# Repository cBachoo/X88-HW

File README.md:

# X88H - Hybrid USB/JST

## License

This work is licensed under a [Creative Commons Attribution-ShareAlike 4.0 International License](https://creativecommons.org/licenses/by-sa/4.0/).

You are free to produce, modify, manufacture, and distribute this design, including for commercial purposes, provided you give appropriate credit and license any derivative works under the same terms.

Questions? Contact Bachoo (`bachoobusiness[at]gmail.com`).

[![CC BY-SA 4.0][cc-by-sa-image]][cc-by-sa]

[cc-by-sa]: http://creativecommons.org/licenses/by-sa/4.0/
[cc-by-sa-image]: https://licensebuttons.net/l/by-sa/4.0/88x31.png
[cc-by-sa-shield]: https://img.shields.io/badge/License-CC%20BY--SA%204.0-lightgrey.svg

## Changelog

- 17 Aug 2024
    - Rotated JST connector so it's facing the alphas

## Design Files / Libraries

The files were designed with [KiCAD 8.0.4](https://www.kicad.org/).

The [marbastlib](https://github.com/ebastler/marbastlib) MX switch symbol/footprint library is used for the project.

The 3D model for the PCB can be seen in the main folder under `X88H-3D-model.step`.

## Ordering from JLCPCB

1) Head to the [JLCPCB order page](https://cart.jlcpcb.com/quote).

2) Upload the `GERBER-X88H.zip` file in `jlcpcb/production_files/`.

3) Set the quantity of the PCBs you want made.

4) Set your desired PCB parameters. Here are some suggested parameters: (Everything else can be kept at their default)

- PCB Color: **Black**
- Surface Finish: **ENIG**
- Remove Order Number: **Yes**   

5) Enable the PCB Assembly option at the bottom, and set the following parameters:

- PCBA Type: **Standard**
- Assembly Side: **Both Sides**

6) Press `Confirm` at the bottom or `NEXT` on the right to get to the next page.

7) Click `NEXT` to get to the Bill of Materials tab.

8) Click `Add BOM File` and select the `BOM-X88H.csv` file in `jlcpcb/production_files/`.

9) Click `Add CPL File` and select the `CPL-X88H.csv` file in `jlcpcb/production_files/`. Click `Process BOM & CPL` to proceed.

10) You should be presented with a list of all the components and quantities needed. Double check there are no missing components. If there are, you will have to find substitute components for it. Click `NEXT` to proceed.

11) You should be presented with a view of the PCB and its components. Click `NEXT` to proceed.

12) You should see a breakdown of the price for the PCBs you want to order. Select `Keyboard - HS Code 847330` under `Office Appliance Accessories` for the Product Description.

13) Save to cart, and pay for it!

## Ordering from PCBWay

1) Head to the [PCBWay Quick Order page](https://www.pcbway.com/QuickOrderOnline.aspx)

2) Click the `Add Gerber file` button and add the `X88H.kicad_pcb.zip` file in the main folder. Don't worry about the broken preview.

3) Set the quantity of the PCBs you want made.

4) Set your desired PCB parameters. Here are some suggested parameters: (Everything else can be kept at their default)

- Solder mask: **Black**
- Surface finish: **Immersion gold (ENIG)**
- Remove product no.: **Yes (extra+$1.5)**

5) Enable the Assembly Service option at the bottom, and set the following parameters:

- Assembly side(s): **Both sides**
- Quantity: **as needed; same number as your PCBs?**
- Do you accept alternatives/substitutes made in China? **Yes**

6) Click Save to Cart. You will have to wait for your order to be reviewed before you can pay for it.

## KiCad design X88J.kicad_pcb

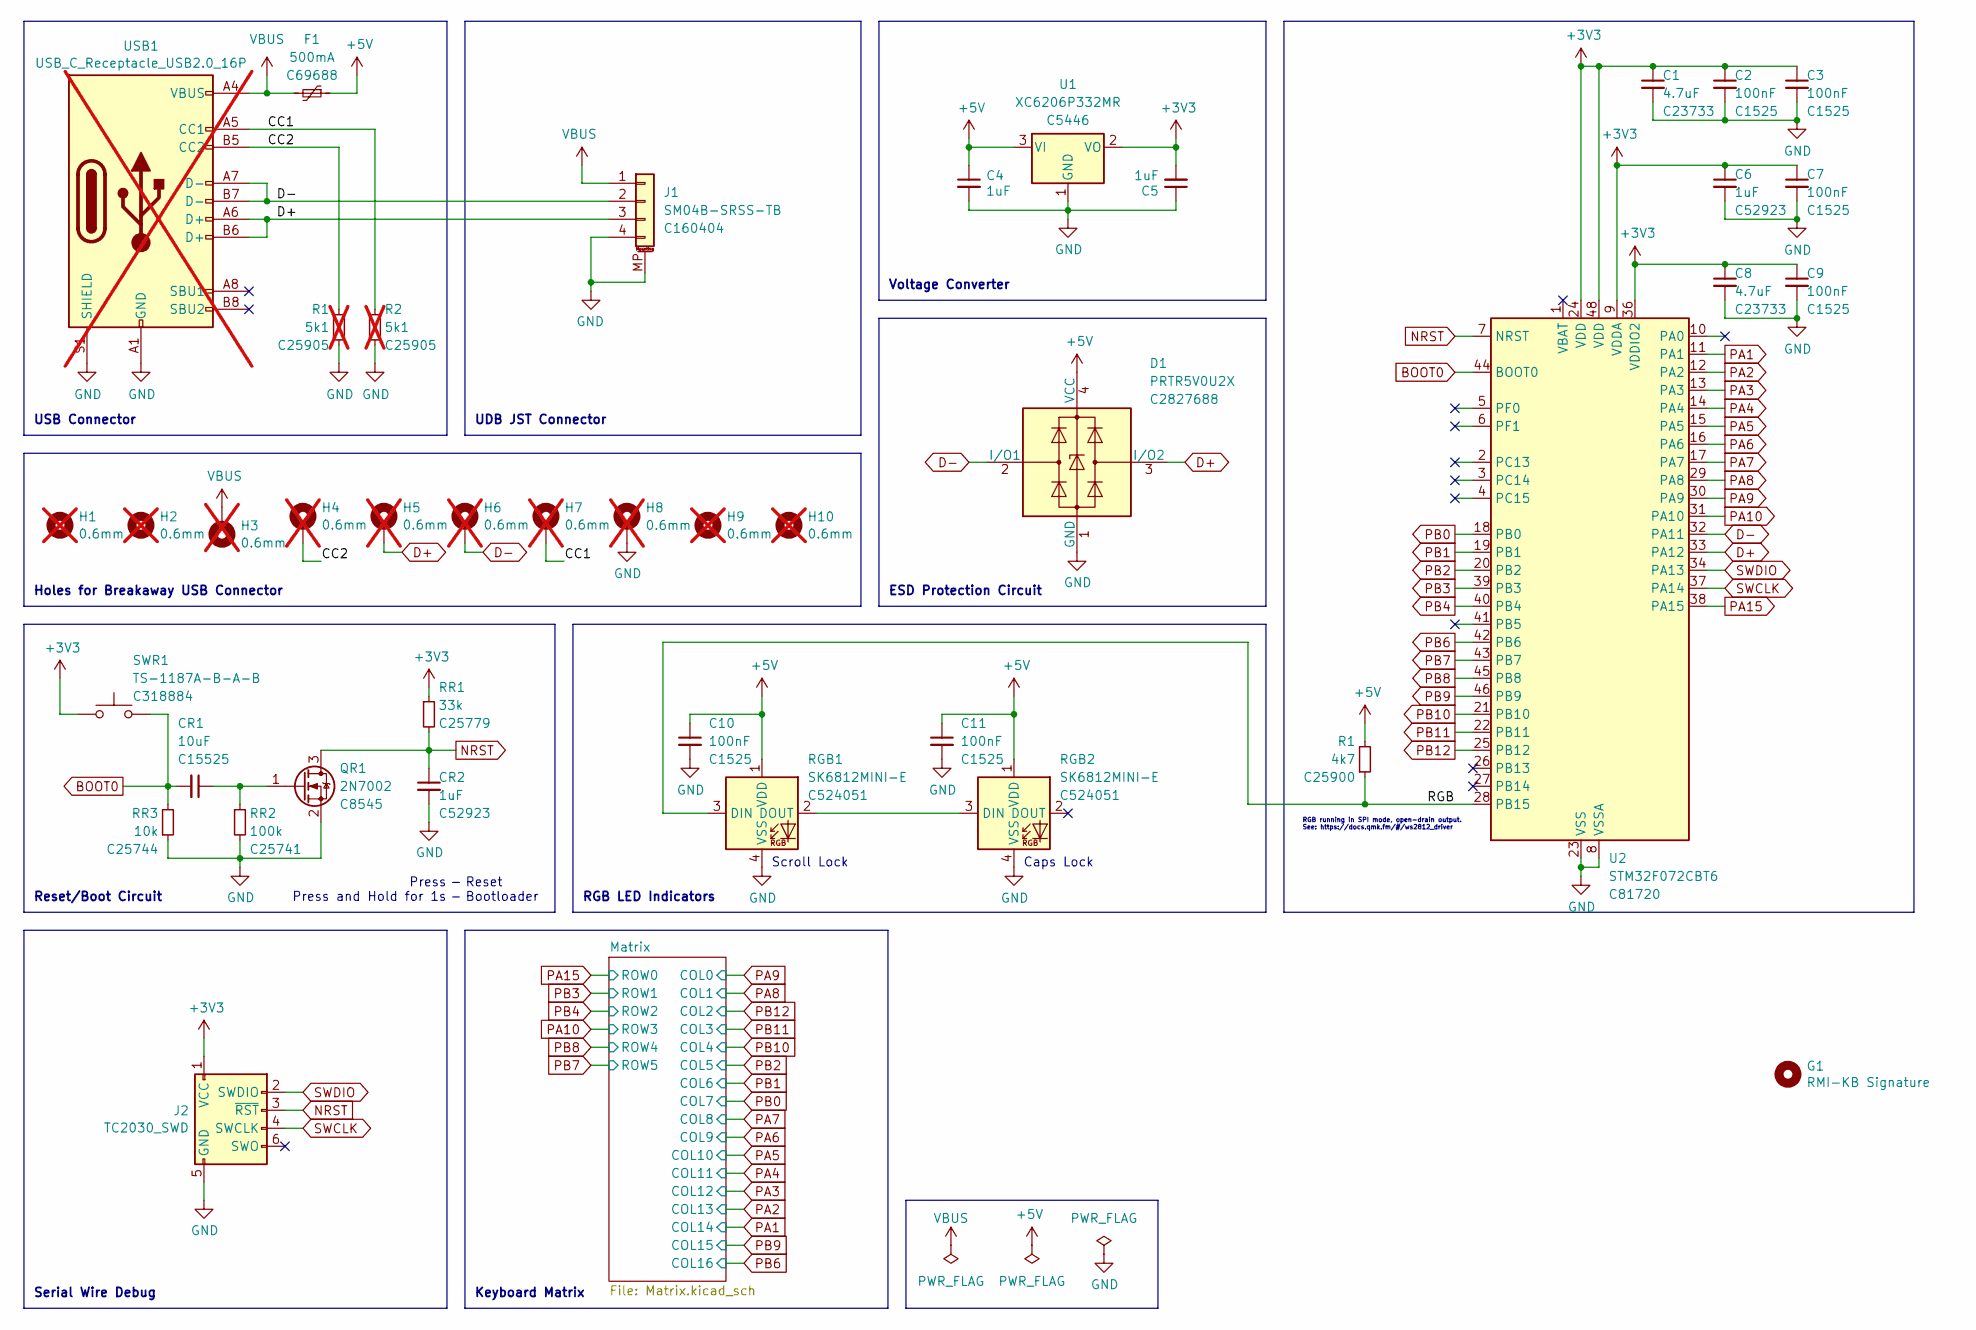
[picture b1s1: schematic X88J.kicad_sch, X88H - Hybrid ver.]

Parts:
C1, C8: 4.7uF; C_0402_1005Metric; MPN CL05A475MP5NRNC; LCSC C23733
C2, C3, C7, C9, C10, C11: 100nF; C_0402_1005Metric; MPN CL05B104KO5NNNC; LCSC C1525
C4, C5, C6: 1uF; C_0402_1005Metric; MPN CL05A105KA5NQNC; LCSC C52923
CR1: 10uF; C_0402_1005Metric; MPN CL05A106MQ5NUNC; LCSC C15525
CR2: 1uF; C_0402_1005Metric; MPN CL05A105KA5NQNC; LCSC C52923
D1: PRTR5V0U2X; SOT-143; MPN PRTR5V0U2X; LCSC C2827688
F1: 500mA; Fuse_1206_3216Metric_Pad1.42x1.75mm_HandSolder; MPN nSMD050; LCSC C69688
G1: RMI-KB Signature; Signature
H1, H2, H9, H10: 0.6mm; Hole_0.6mm; not fitted
H3, H4, H5, H6, H7, H8: 0.6mm; Hole_0.6mm_Pad; not fitted
J1: SM04B-SRSS-TB; JST_SH_SM04B-SRSS-TB_1x04-1MP_P1.00mm_Horizontal; MPN SM04B-SRSS-TB(LF)(SN); LCSC C160404
J2: TC2030_SWD; CON_TC2030_outlined
QR1: 2N7002; SOT-23; MPN 2N7002; LCSC C8545
R1, R2: 5k1; R_0402_1005Metric; MPN 0402WGF5101TCE; LCSC C25905; not fitted
RGB1, RGB2: SK6812MINI-E; LED_6028R; MPN SK6812MINI-E; LCSC C524051
RR1: 33k; R_0402_1005Metric; MPN 0402WGF3302TCE; LCSC C25779
RR2: 100k; R_0402_1005Metric; MPN 0402WGF1003TCE; LCSC C25741
RR3: 10k; R_0402_1005Metric; MPN 0402WGF1002TCE; LCSC C25744
SWR1: TS-1187A-B-A-B; SW_SPST_TL3342; MPN TS-1187A-B-A-B; LCSC C318884
U1: XC6206P332MR; SOT-23; MPN XC6206P332MR-G; LCSC C5446
U2: STM32F072CBT6; LQFP-48_7x7mm_P0.5mm; MPN STM32F072CBT6; LCSC C81720
USB1: USB_C_Receptacle_USB2.0_16P; USB_C_Receptacle_HRO_TYPE-C-31-M-12; MPN TYPE-C-31-M-12; LCSC C165948; not fitted

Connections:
+3V3: C1.1, C2.1, C3.1, C5.2, C6.1, C7.1, C8.1, C9.1, J2.1 (VCC), RR1.1, SWR1.1, U1.2 (VO), U2.9 (VDDA), U2.24 (VDD), U2.36 (VDDIO2), U2.48 (VDD)
+5V: C4.1, C10.1, C11.1, D1.4 (VCC), F1.1, RGB1.1 (VDD), RGB2.1 (VDD), U1.3 (VI); also elsewhere on the board
/RGB: RGB1.3 (DIN), U2.28 (PB15); also elsewhere on the board
D+: D1.3 (I/O2), H5.1, J1.3, U2.33 (PA12), USB1.A6 (D+), USB1.B6 (D+)
D-: D1.2 (I/O1), H6.1, J1.2, U2.32 (PA11), USB1.A7 (D-), USB1.B7 (D-)
NRST: CR2.1, J2.3 (~RST), QR1.3 (D), RR1.2, U2.7 (NRST)
unnamed: H4.1, R1.1, USB1.B5 (CC2)
unnamed: H7.1, R2.1, USB1.A5 (CC1)
unnamed: RGB1.2 (DOUT), RGB2.3 (DIN)
PA1: U2.11 (PA1); also elsewhere on the board
PA2: U2.12 (PA2); also elsewhere on the board
PA3: U2.13 (PA3); also elsewhere on the board
PA4: U2.14 (PA4); also elsewhere on the board
PA5: U2.15 (PA5); also elsewhere on the board
PA6: U2.16 (PA6); also elsewhere on the board
PA7: U2.17 (PA7); also elsewhere on the board
PA8: U2.29 (PA8); also elsewhere on the board
PA9: U2.30 (PA9); also elsewhere on the board
PA10: U2.31 (PA10); also elsewhere on the board
PA15: U2.38 (PA15); also elsewhere on the board
PB0: U2.18 (PB0); also elsewhere on the board
PB1: U2.19 (PB1); also elsewhere on the board
PB2: U2.20 (PB2); also elsewhere on the board
PB3: U2.39 (PB3); also elsewhere on the board
PB4: U2.40 (PB4); also elsewhere on the board
PB6: U2.42 (PB6); also elsewhere on the board
PB7: U2.43 (PB7); also elsewhere on the board
PB8: U2.45 (PB8); also elsewhere on the board
PB9: U2.46 (PB9); also elsewhere on the board
PB10: U2.21 (PB10); also elsewhere on the board
PB11: U2.22 (PB11); also elsewhere on the board
PB12: U2.25 (PB12); also elsewhere on the board
SWCLK: J2.4 (SWCLK), U2.37 (PA14)
SWDIO: J2.2 (SWDIO), U2.34 (PA13)
VBUS: F1.2, H3.1, J1.1, USB1.A4 (VBUS), USB1.A9 (VBUS), USB1.B4 (VBUS), USB1.B9 (VBUS)

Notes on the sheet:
Holes for Breakaway USB Connector
Reset Bootloader
ESD Protection Circuit
Caps Lock
RGB running in SPI mode, open-drain output. See: https://docs.qmk.fm/#/ws2812_driver
- -
UDB JST Connector
RGB LED Indicators
Voltage Converter
Press Press and Hold for 1s
Reset/Boot Circuit
Serial Wire Debug
Keyboard Matrix
USB Connector
Scroll Lock

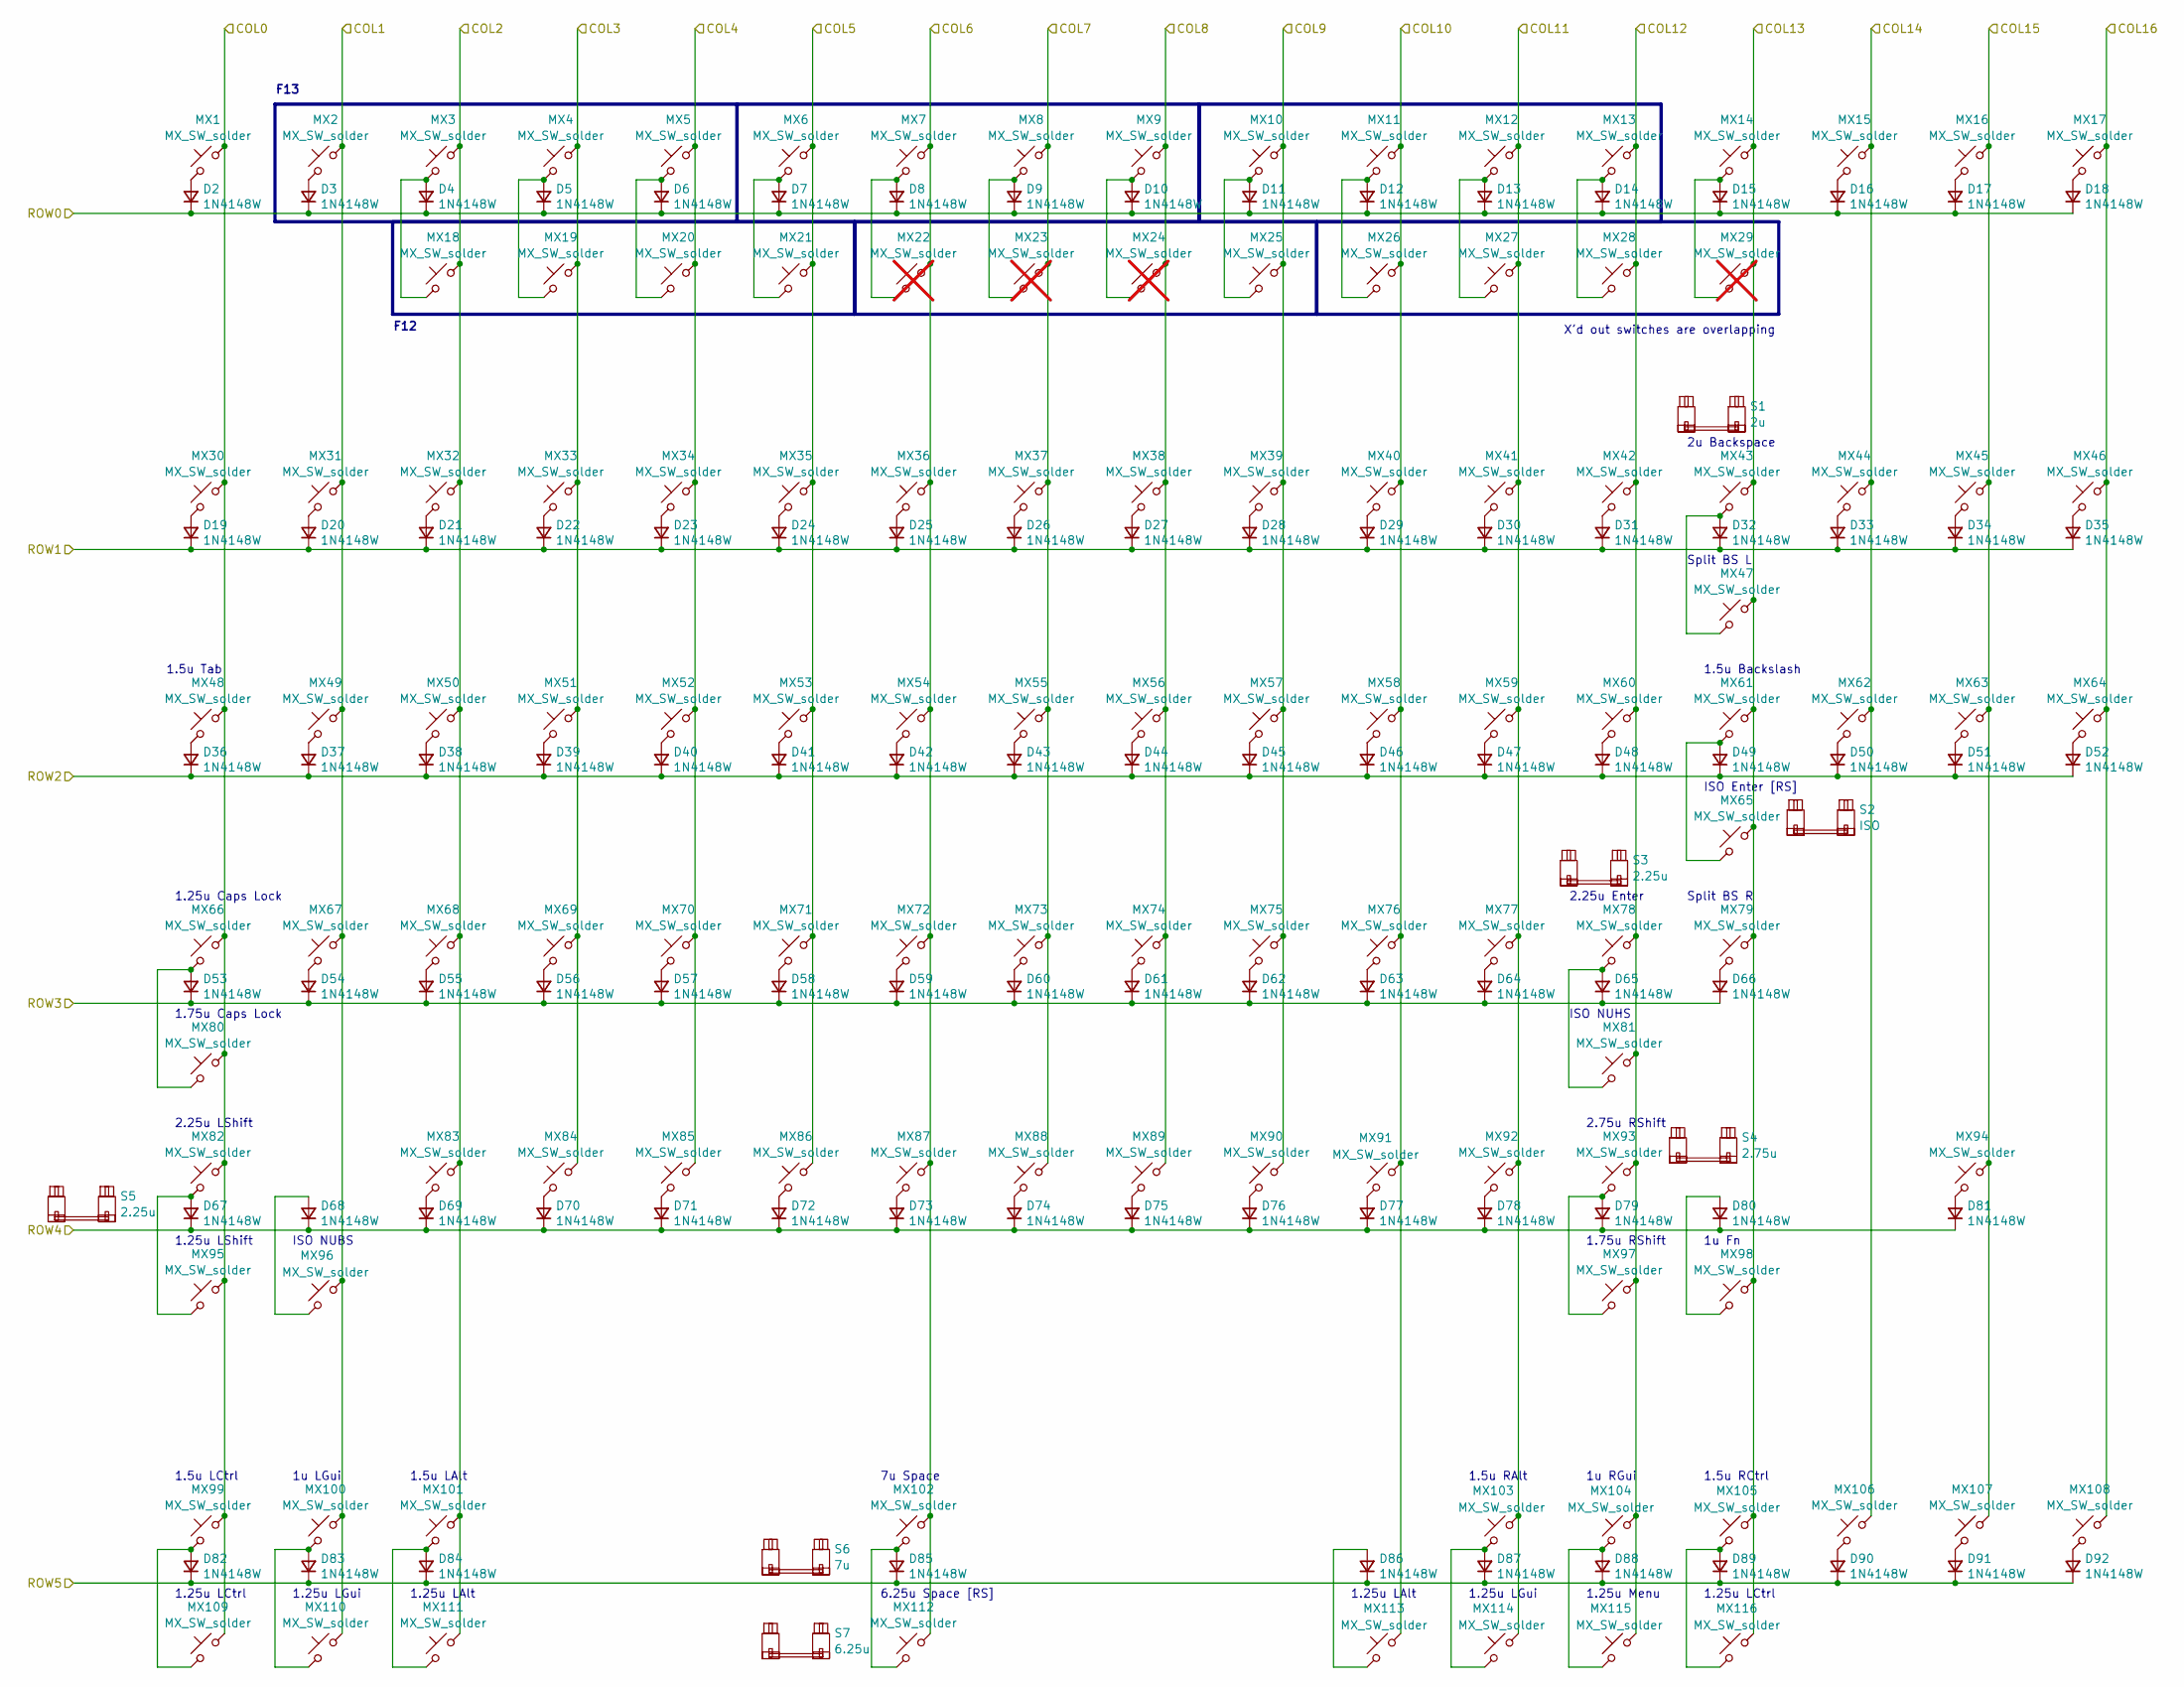
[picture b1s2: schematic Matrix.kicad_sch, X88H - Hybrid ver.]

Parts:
D2, D3, D4, D5, D6, D7, D8, D9, D10, D11, D12, D13, D14, D15, D16, D17, D18, D19, D20, D21, D22, D23, D24, D25, D26, D27, D28, D29, D30, D31, D32, D33, D34, D35, D36, D37, D38, D39, D40, D41, D42, D43, D44, D45, D46, D47, D48, D49, D50, D51, D52, D53, D54, D55, D56, D57, D58, D59, D60, D61, D62, D63, D64, D65, D66, D67, D68, D69, D70, D71, D72, D73, D74, D75, D76, D77, D78, D79, D80, D81, D82, D83, D84, D85, D86, D87, D88, D89, D90, D91, D92: 1N4148W; D_SOD-123; MPN 1N4148W; LCSC C81598
MX1, MX2, MX3, MX4, MX5, MX6, MX7, MX8, MX9, MX10, MX11, MX12, MX13, MX14, MX15, MX16, MX17, MX18, MX19, MX20, MX21, MX25, MX26, MX27, MX28, MX30, MX31, MX32, MX33, MX34, MX35, MX36, MX37, MX38, MX39, MX40, MX41, MX42, MX43, MX44, MX45, MX46, MX47, MX49, MX50, MX51, MX52, MX53, MX54, MX55, MX56, MX57, MX58, MX59, MX60, MX62, MX63, MX64, MX65, MX67, MX68, MX69, MX70, MX71, MX72, MX73, MX74, MX75, MX76, MX77, MX78, MX79, MX81, MX82, MX83, MX84, MX85, MX86, MX87, MX88, MX89, MX90, MX91, MX92, MX93, MX94, MX96, MX98, MX100, MX102, MX104, MX106, MX107, MX108, MX112: MX_SW_solder; SW_MX_1u
MX22, MX23, MX24, MX29: MX_SW_solder; SW_MX_1u; not fitted
MX48, MX61, MX99, MX101, MX103, MX105: MX_SW_solder; SW_MX_1.5u
MX66: MX_SW_solder; SW_MX_1.75u_STP_1.25
MX80, MX97: MX_SW_solder; SW_MX_1.75u
MX95, MX109, MX110, MX111, MX113, MX114, MX115, MX116: MX_SW_solder; SW_MX_1.25u
S1: 2u; STAB_MX_2u
S2: ISO; STAB_MX_ISO-ROT
S3, S5: 2.25u; STAB_MX_2.25u
S4: 2.75u; STAB_MX_2.75u
S6: 7u; STAB_MX_7u
S7: 6.25u; STAB_MX_6.25u

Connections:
unnamed: D2.2 (A), MX1.2
unnamed: D3.2 (A), MX2.2
unnamed: D4.2 (A), MX3.2, MX18.2
unnamed: D5.2 (A), MX4.2, MX19.2
unnamed: D6.2 (A), MX5.2, MX20.2
unnamed: D7.2 (A), MX6.2, MX21.2
unnamed: D8.2 (A), MX7.2, MX22.2
unnamed: D9.2 (A), MX8.2, MX23.2
unnamed: D10.2 (A), MX9.2, MX24.2
unnamed: D11.2 (A), MX10.2, MX25.2
unnamed: D12.2 (A), MX11.2, MX26.2
unnamed: D13.2 (A), MX12.2, MX27.2
unnamed: D14.2 (A), MX13.2, MX28.2
unnamed: D15.2 (A), MX14.2, MX29.2
unnamed: D16.2 (A), MX15.2
unnamed: D17.2 (A), MX16.2
unnamed: D18.2 (A), MX17.2
unnamed: D19.2 (A), MX30.2
unnamed: D20.2 (A), MX31.2
unnamed: D21.2 (A), MX32.2
unnamed: D22.2 (A), MX33.2
unnamed: D23.2 (A), MX34.2
unnamed: D24.2 (A), MX35.2
unnamed: D25.2 (A), MX36.2
unnamed: D26.2 (A), MX37.2
unnamed: D27.2 (A), MX38.2
unnamed: D28.2 (A), MX39.2
unnamed: D29.2 (A), MX40.2
unnamed: D30.2 (A), MX41.2
unnamed: D31.2 (A), MX42.2
unnamed: D32.2 (A), MX43.2, MX47.2
unnamed: D33.2 (A), MX44.2
unnamed: D34.2 (A), MX45.2
unnamed: D35.2 (A), MX46.2
unnamed: D36.2 (A), MX48.2
unnamed: D37.2 (A), MX49.2
unnamed: D38.2 (A), MX50.2
unnamed: D39.2 (A), MX51.2
unnamed: D40.2 (A), MX52.2
unnamed: D41.2 (A), MX53.2
unnamed: D42.2 (A), MX54.2
unnamed: D43.2 (A), MX55.2
unnamed: D44.2 (A), MX56.2
unnamed: D45.2 (A), MX57.2
unnamed: D46.2 (A), MX58.2
unnamed: D47.2 (A), MX59.2
unnamed: D48.2 (A), MX60.2
unnamed: D49.2 (A), MX61.2, MX65.2
unnamed: D50.2 (A), MX62.2
unnamed: D51.2 (A), MX63.2
unnamed: D52.2 (A), MX64.2
unnamed: D53.2 (A), MX66.2, MX80.2
unnamed: D54.2 (A), MX67.2
unnamed: D55.2 (A), MX68.2
unnamed: D56.2 (A), MX69.2
unnamed: D57.2 (A), MX70.2
unnamed: D58.2 (A), MX71.2
unnamed: D59.2 (A), MX72.2
unnamed: D60.2 (A), MX73.2
unnamed: D61.2 (A), MX74.2
unnamed: D62.2 (A), MX75.2
unnamed: D63.2 (A), MX76.2
unnamed: D64.2 (A), MX77.2
unnamed: D65.2 (A), MX78.2, MX81.2
unnamed: D66.2 (A), MX79.2
unnamed: D67.2 (A), MX82.2, MX95.2
unnamed: D68.2 (A), MX96.1
unnamed: D69.2 (A), MX83.2
unnamed: D70.2 (A), MX84.2
unnamed: D71.2 (A), MX85.2
unnamed: D72.2 (A), MX86.2
unnamed: D73.2 (A), MX87.2
unnamed: D74.2 (A), MX88.2
unnamed: D75.2 (A), MX89.2
unnamed: D76.2 (A), MX90.2
unnamed: D77.2 (A), MX91.1
unnamed: D78.2 (A), MX92.2
unnamed: D79.2 (A), MX93.2, MX97.2
unnamed: D80.2 (A), MX98.2
unnamed: D81.2 (A), MX94.2
unnamed: D82.2 (A), MX99.2, MX109.2
unnamed: D83.2 (A), MX100.2, MX110.2
unnamed: D84.2 (A), MX101.2, MX111.2
unnamed: D85.2 (A), MX102.2, MX112.2
unnamed: D86.2 (A), MX113.1
unnamed: D87.2 (A), MX103.1, MX114.1
unnamed: D88.2 (A), MX104.1, MX115.1
unnamed: D89.2 (A), MX105.1, MX116.1
unnamed: D90.2 (A), MX106.2
unnamed: D91.2 (A), MX107.2
unnamed: D92.2 (A), MX108.2
PA1: MX15.1, MX44.1, MX62.1, MX106.1; also elsewhere on the board
PA2: MX14.1, MX29.1, MX43.1, MX47.1, MX61.1, MX65.1, MX79.1, MX98.1, MX105.2, MX116.2; also elsewhere on the board
PA3: MX13.1, MX28.1, MX42.1, MX60.1, MX78.1, MX81.1, MX93.1, MX97.1, MX104.2, MX115.2; also elsewhere on the board
PA4: MX12.1, MX27.1, MX41.1, MX59.1, MX77.1, MX92.1, MX103.2, MX114.2; also elsewhere on the board
PA5: MX11.1, MX26.1, MX40.1, MX58.1, MX76.1, MX91.2, MX113.2; also elsewhere on the board
PA6: MX10.1, MX25.1, MX39.1, MX57.1, MX75.1, MX90.1; also elsewhere on the board
PA7: MX9.1, MX24.1, MX38.1, MX56.1, MX74.1, MX89.1; also elsewhere on the board
PA8: MX2.1, MX31.1, MX49.1, MX67.1, MX96.2, MX100.1, MX110.1; also elsewhere on the board
PA9: MX1.1, MX30.1, MX48.1, MX66.1, MX80.1, MX82.1, MX95.1, MX99.1, MX109.1; also elsewhere on the board
PA10: D53.1 (K), D54.1 (K), D55.1 (K), D56.1 (K), D57.1 (K), D58.1 (K), D59.1 (K), D60.1 (K), D61.1 (K), D62.1 (K), D63.1 (K), D64.1 (K), D65.1 (K), D66.1 (K); also elsewhere on the board
PA15: D2.1 (K), D3.1 (K), D4.1 (K), D5.1 (K), D6.1 (K), D7.1 (K), D8.1 (K), D9.1 (K), D10.1 (K), D11.1 (K), D12.1 (K), D13.1 (K), D14.1 (K), D15.1 (K), D16.1 (K), D17.1 (K), D18.1 (K); also elsewhere on the board
PB0: MX8.1, MX23.1, MX37.1, MX55.1, MX73.1, MX88.1; also elsewhere on the board
PB1: MX7.1, MX22.1, MX36.1, MX54.1, MX72.1, MX87.1, MX102.1, MX112.1; also elsewhere on the board
PB2: MX6.1, MX21.1, MX35.1, MX53.1, MX71.1, MX86.1; also elsewhere on the board
PB3: D19.1 (K), D20.1 (K), D21.1 (K), D22.1 (K), D23.1 (K), D24.1 (K), D25.1 (K), D26.1 (K), D27.1 (K), D28.1 (K), D29.1 (K), D30.1 (K), D31.1 (K), D32.1 (K), D33.1 (K), D34.1 (K), D35.1 (K); also elsewhere on the board
PB4: D36.1 (K), D37.1 (K), D38.1 (K), D39.1 (K), D40.1 (K), D41.1 (K), D42.1 (K), D43.1 (K), D44.1 (K), D45.1 (K), D46.1 (K), D47.1 (K), D48.1 (K), D49.1 (K), D50.1 (K), D51.1 (K), D52.1 (K); also elsewhere on the board
PB6: MX17.1, MX46.1, MX64.1, MX108.1; also elsewhere on the board
PB7: D82.1 (K), D83.1 (K), D84.1 (K), D85.1 (K), D86.1 (K), D87.1 (K), D88.1 (K), D89.1 (K), D90.1 (K), D91.1 (K), D92.1 (K); also elsewhere on the board
PB8: D67.1 (K), D68.1 (K), D69.1 (K), D70.1 (K), D71.1 (K), D72.1 (K), D73.1 (K), D74.1 (K), D75.1 (K), D76.1 (K), D77.1 (K), D78.1 (K), D79.1 (K), D80.1 (K), D81.1 (K); also elsewhere on the board
PB9: MX16.1, MX45.1, MX63.1, MX94.1, MX107.1; also elsewhere on the board
PB10: MX5.1, MX20.1, MX34.1, MX52.1, MX70.1, MX85.1; also elsewhere on the board
PB11: MX4.1, MX19.1, MX33.1, MX51.1, MX69.1, MX84.1; also elsewhere on the board
PB12: MX3.1, MX18.1, MX32.1, MX50.1, MX68.1, MX83.1, MX101.1, MX111.1; also elsewhere on the board

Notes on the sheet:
2u Backspace
1.5u LAlt
Split BS R
1u LGui
1.75u RShift
1.5u RAlt
ISO Enter [RS]
1.25u LCtrl
7u Space
1.75u Caps Lock
6.25u Space [RS]
F13
1.25u Caps Lock
ISO NUBS
1.5u Backslash
1.25u LGui
2.75u RShift
1u RGui
1.5u Tab
X'd out switches are overlapping
ISO NUHS
2.25u LShift
1.25u LAlt
1.25u LShift
1.25u Menu
1.5u LCtrl
1.5u RCtrl
2.25u Enter
Split BS L
1u Fn
F12

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
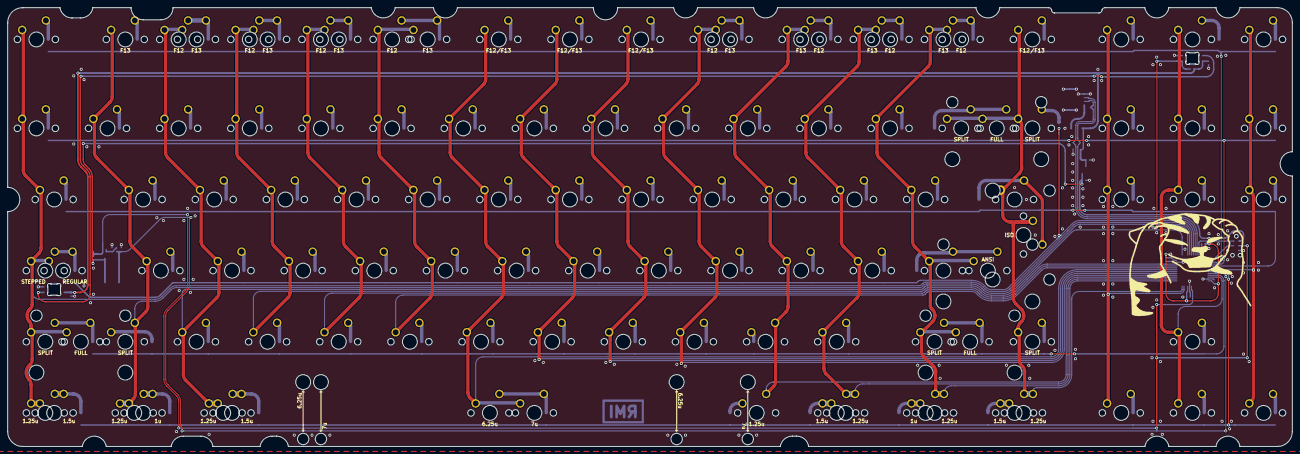
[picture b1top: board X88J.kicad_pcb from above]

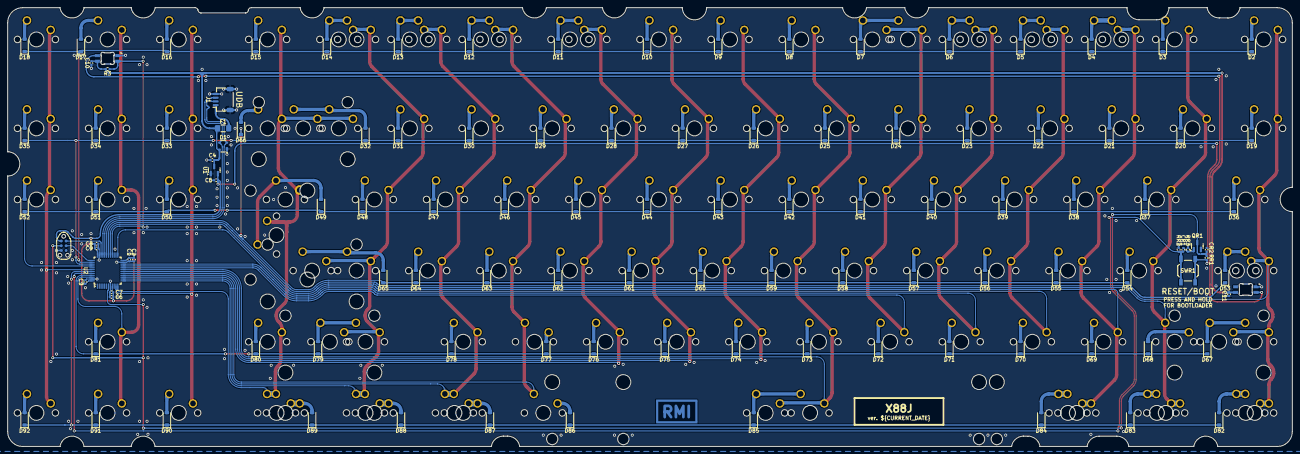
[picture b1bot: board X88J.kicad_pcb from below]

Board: 2 copper layers, 344.0 x 117.5 mm, 238 parts (119 on the bottom side), 127 nets.

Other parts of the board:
R3: 4k7; R_0402_1005Metric

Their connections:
+5V: R3.2; also elsewhere on the board
/RGB: R3.1; also elsewhere on the board

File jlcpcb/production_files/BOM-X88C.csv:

Comment,Designator,Footprint,LCSC
100nF,"C10,C11,C2,C3,C7,C9",C_0402_1005Metric,C1525
10uF,CR1,C_0402_1005Metric,C15525
USB_C_Receptacle_USB2.0_16P,USB1,USB_C_Receptacle_HRO_TYPE-C-31-M-12,C165948
4.7uF,"C1,C8",C_0402_1005Metric,C23733
100k,RR3,R_0402_1005Metric,C25741
10k,RR2,R_0402_1005Metric,C25744
33k,RR1,R_0402_1005Metric,C25779
4k7,R3,R_0402_1005Metric,C25900
5k1,"R1,R2",R_0402_1005Metric,C25905
PRTR5V0U2X,D1,SOT-143,C2827688
TS-1187A-B-A-B,SWR1,SW_SPST_TL3342,C318884
SK6812MINI-E,"RGB1,RGB2",LED_6028R,C524051
1uF,"C4,C5,C6,CR2",C_0402_1005Metric,C52923
XC6206P332MR,U1,SOT-23,C5446
500mA,F1,Fuse_1206_3216Metric_Pad1.42x1.75mm_HandSolder,C69688
1N4148W,"D10,D11,D12,D13,D14,D15,D16,D17,D18,D19,D2,D20,D21,D22,D23,D24,D25,D26,D27,D28,D29,D3,D30,D31,D32,D33,D34,D35,D36,D37,D38,D39,D4,D40,D41,D42,D43,D44,D45,D46,D47,D48,D49,D5,D50,D51,D52,D53,D54,D55,D56,D57,D58,D59,D6,D60,D61,D62,D63,D64,D65,D66,D67,D68,D69,D7,D70,D71,D72,D73,D74,D75,D76,D77,D78,D79,D8,D80,D81,D82,D83,D84,D85,D86,D87,D88,D89,D9,D90,D91,D92",D_SOD-123,C81598
STM32F072CBT6,U2,LQFP-48_7x7mm_P0.5mm,C81720
2N7002,QR1,SOT-23,C8545

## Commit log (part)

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2024-07-23 Add Type-C only variant
2024-07-23 Add JST only variant
2024-07-25 Generate PCB STEP file
2024-08-16 Rotate JST to face alphas
2024-08-16 Regenerate STEP file with rotated JST
2024-08-17 Regenerate gerbers with teardrops
